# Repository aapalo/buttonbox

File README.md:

# Button box

The TM Cougar Throttle USB-mod has been forked into its own repository, which can be found from here: 
<https://github.com/aapalo/cougar-usb>

Features:
- Can be used to convert a TM Cougar Throttle into a USB device, or as a stand-alone button box.
- Several boards can be daisy-chained via the 1x5 pin socket J11.
- The dimensions of the PCB are 112mm * 37mm.

v1.0 errata:
- Pro micro pin 9, PM_C7, should be PM_D7

----

The required components include:
- Arduino board, Pro Micro 5V/16MHz ATmega32U4
- Shift register, 74HC165N, DIP-16
- SMD resistors, 10k Ohm, 0805
- SMD capacitors, 470nF, 0805
- Pin sockets and/or headers, 2.54mm pitch
- Buttons/switches
- Jumper wires for the buttons/switches

----

The recommended software to program the Pro Micro is MMJoy2:
<https://simhq.com/forum/ubbthreads.php/topics/3899105/mmjoy-mmjoy2-build-your-own-usb-controller>

When used as a stand-alone button box, the board should fit inside a Hammond [1591C*](1) or a [1591XXC](2) enclosure.

[1]: <http://www.hammondmfg.com/dwg2.htm>
[2]: <https://www.hammfg.com/part/1591XXCBK>
[3]: <http://www.hammondmfg.com/dwg2XX.htm>

----

[//]: # (Todo: add pictures of a soldered version)

A soldered and installed version in use:

The schematic, with some of the planned DCS key bindings visible:

Top side, with the 3d view and layout view:

Bottom side, with the 3d view and layout view:

Both the top and bottom layer visible:

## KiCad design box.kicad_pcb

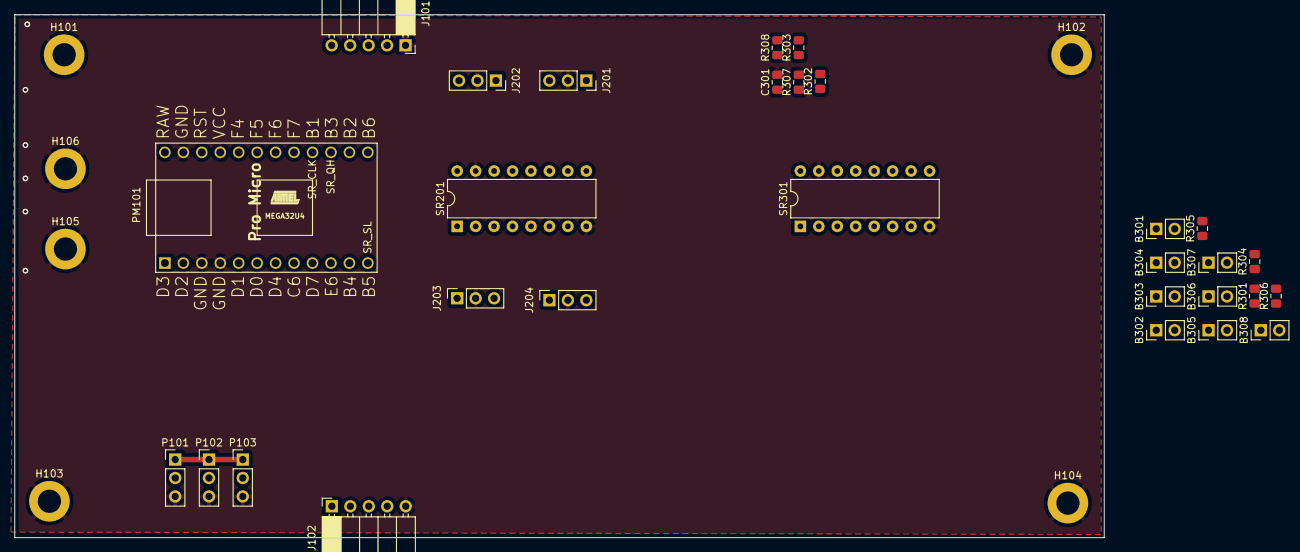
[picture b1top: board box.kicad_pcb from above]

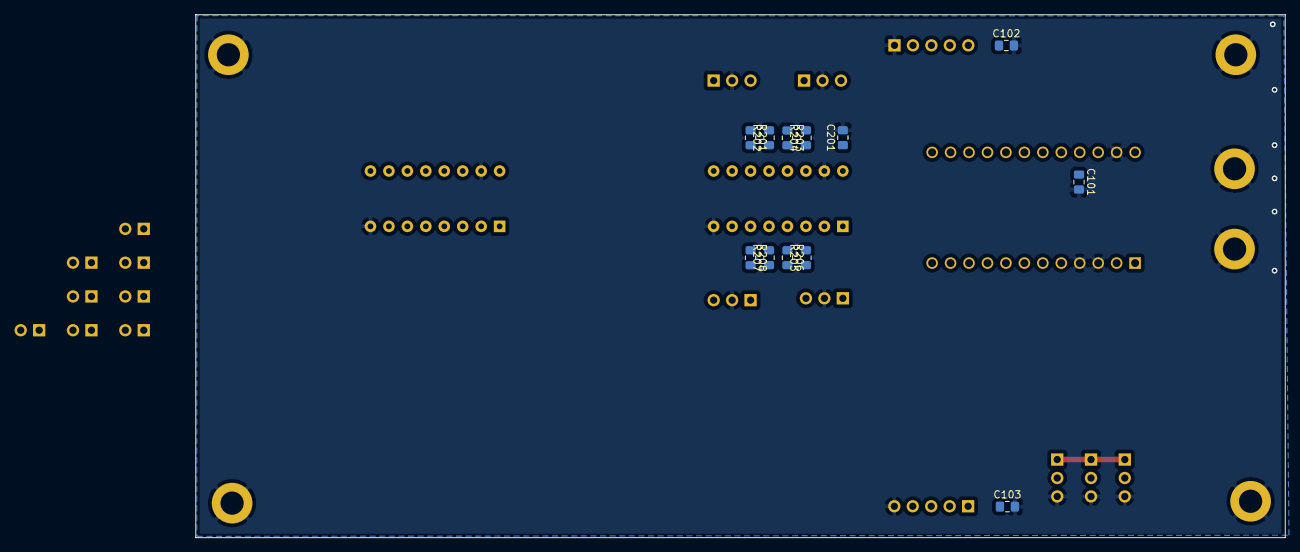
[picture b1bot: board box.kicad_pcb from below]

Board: 2 copper layers, 150.0 x 72.0 mm, 47 parts (12 on the bottom side), 23 nets.

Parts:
B301, B302, B303, B304, B305, B306, B307, B308: Conn_01x02; PinHeader_1x02_P2.54mm_Vertical
C101, C102, C103, C201, C301: 470n; C_0805_2012Metric_Pad1.15x1.40mm_HandSolder
H101, H102, H103, H104, H105, H106: MountingHole_Pad; MountingHole_3.2mm_M3_DIN965_Pad
J101, J102: Conn_01x05; PinSocket_1x05_P2.54mm_Horizontal
J201, J202, J203, J204: Conn_01x03; PinSocket_1x03_P2.54mm_Vertical
P101, P102, P103: Conn_01x03_Male; PinHeader_1x03_P2.54mm_Vertical
PM101: Pro_Micro; promicro
R201, R202, R203, R204, R205, R206, R207, R208, R301, R302, R303, R304, R305, R306, R307, R308: 10k; R_0805_2012Metric_Pad1.15x1.40mm_HandSolder
SR201, SR301: Conn_02x08_Counter_Clockwise; DIP-16_W7.62mm

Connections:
+5V: C101.1, C102.1, C103.1, C201.1, C301.1, J101.5, J102.1, P101.1, P102.1, P103.1, PM101.21, R201.1, R202.2, R203.1, R204.2, R205.1, R206.2, R207.1, R208.2, R301.1, R302.1, R303.1, R304.1, R305.1, R306.1, R307.1, R308.1, SR201.16, SR301.16
/CAT: B308.2, R308.2, SR301.6
/Eight buttons/SR_DATA_IN: SR201.10, SR301.9
/H1: B301.2, R301.2, SR301.11
/H2: B302.2, R302.2, SR301.12
/H3: B303.2, R303.2, SR301.13
/H4: B304.2, R304.2, SR301.14
/H5: B305.2, R305.2, SR301.3
/H6: B306.2, R306.2, SR301.4
/H7: B307.2, R307.2, SR301.5
/PM_B1: J101.3, J102.3, PM101.16, SR201.2, SR301.2
/PM_B3: J102.4, PM101.15, SR301.10
/PM_B5: J101.4, J102.2, PM101.12, SR201.1, SR301.1
/SR_SER2: J101.2, SR201.9
/flaps_dn: J203.3, R206.1, SR201.4
/flaps_up: J203.1, R205.2, SR201.3
/gear_dn: J202.3, R204.1, SR201.14
/gear_up: J202.1, R203.2, SR201.13
/hdg_left: J204.1, R207.2, SR201.5
/hdg_right: J204.3, R208.1, SR201.6
/hook_dn: J201.3, R202.1, SR201.12
/hook_up: J201.1, R201.2, SR201.11
GND: B301.1, B302.1, B303.1, B304.1, B305.1, B306.1, B307.1, B308.1, C101.2, C102.2, C103.2, C201.2, C301.2, H101.1, H102.1, H103.1, H104.1, H105.1, H106.1, J101.1, J102.5, J201.2, J202.2, J203.2, J204.2, P101.3, P102.3, P103.3, PM101.3, PM101.4, PM101.23, SR201.8, SR201.15, SR301.8, SR301.15

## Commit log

2020-01-13 Initial release
2020-01-23 Create LICENSE
2020-01-31 C7->D7
2020-03-21 Update March 21st
